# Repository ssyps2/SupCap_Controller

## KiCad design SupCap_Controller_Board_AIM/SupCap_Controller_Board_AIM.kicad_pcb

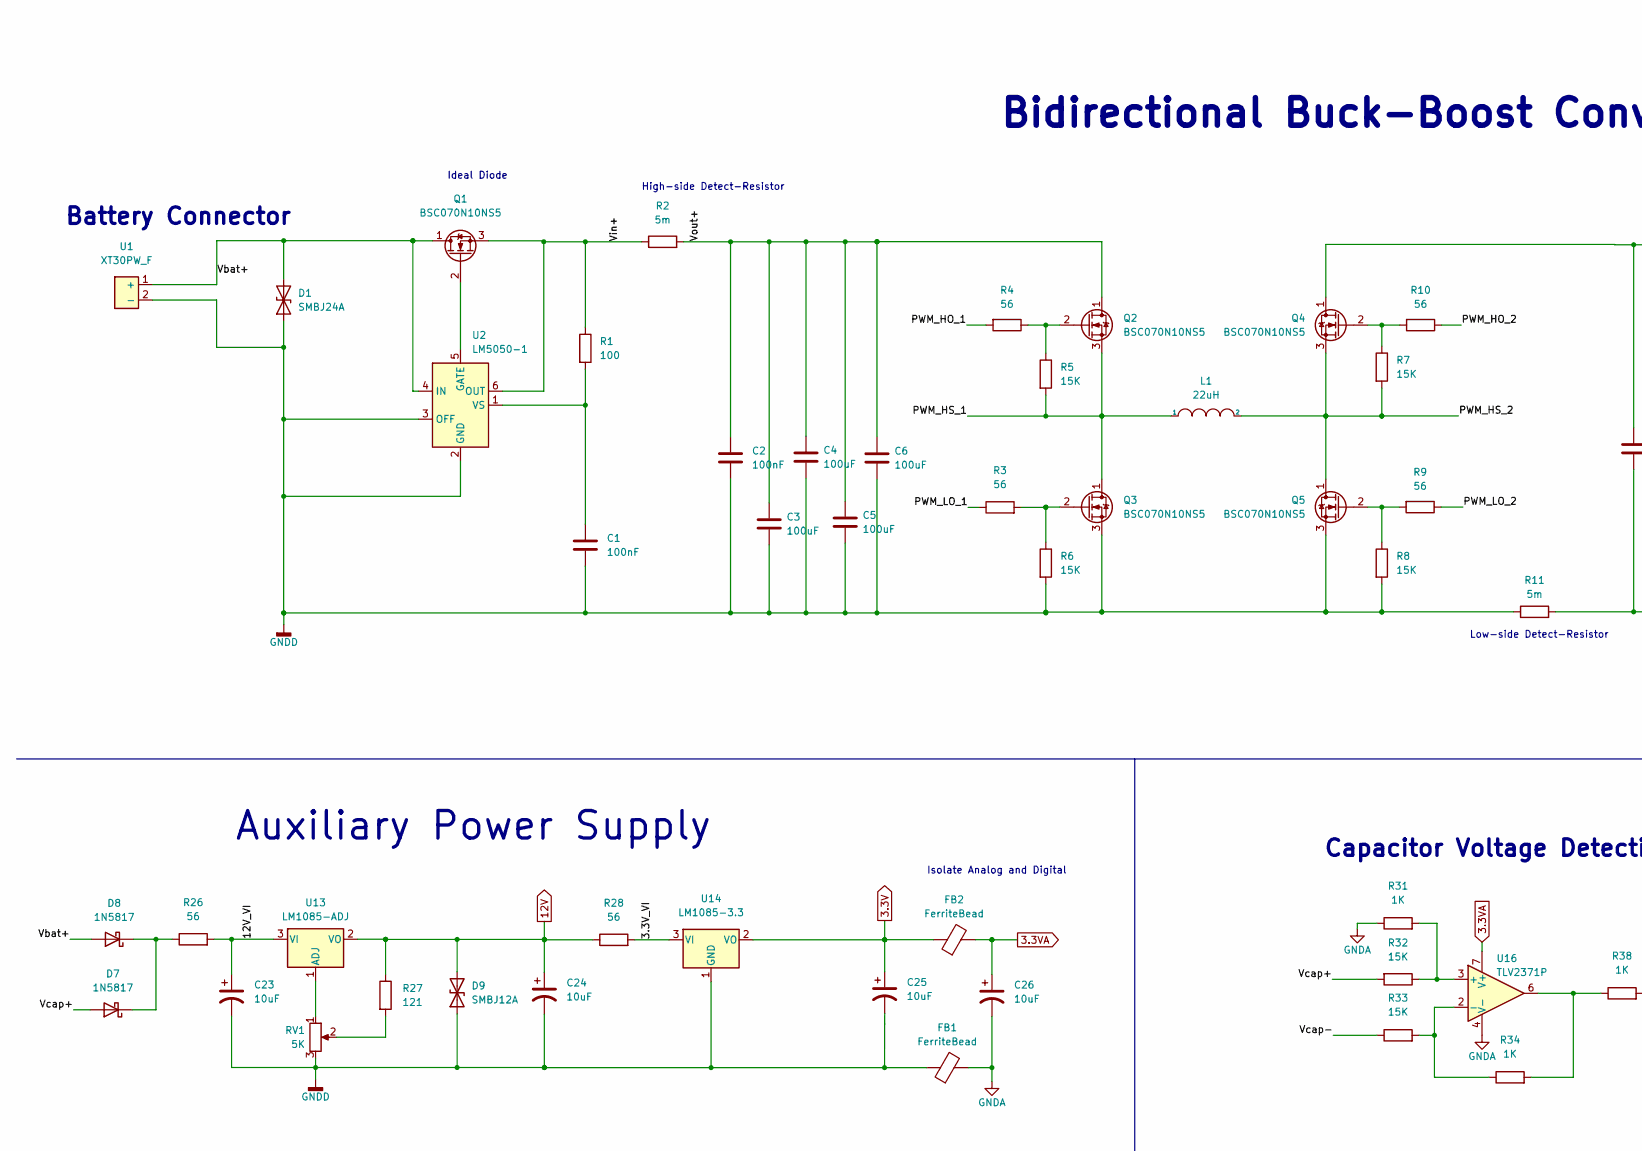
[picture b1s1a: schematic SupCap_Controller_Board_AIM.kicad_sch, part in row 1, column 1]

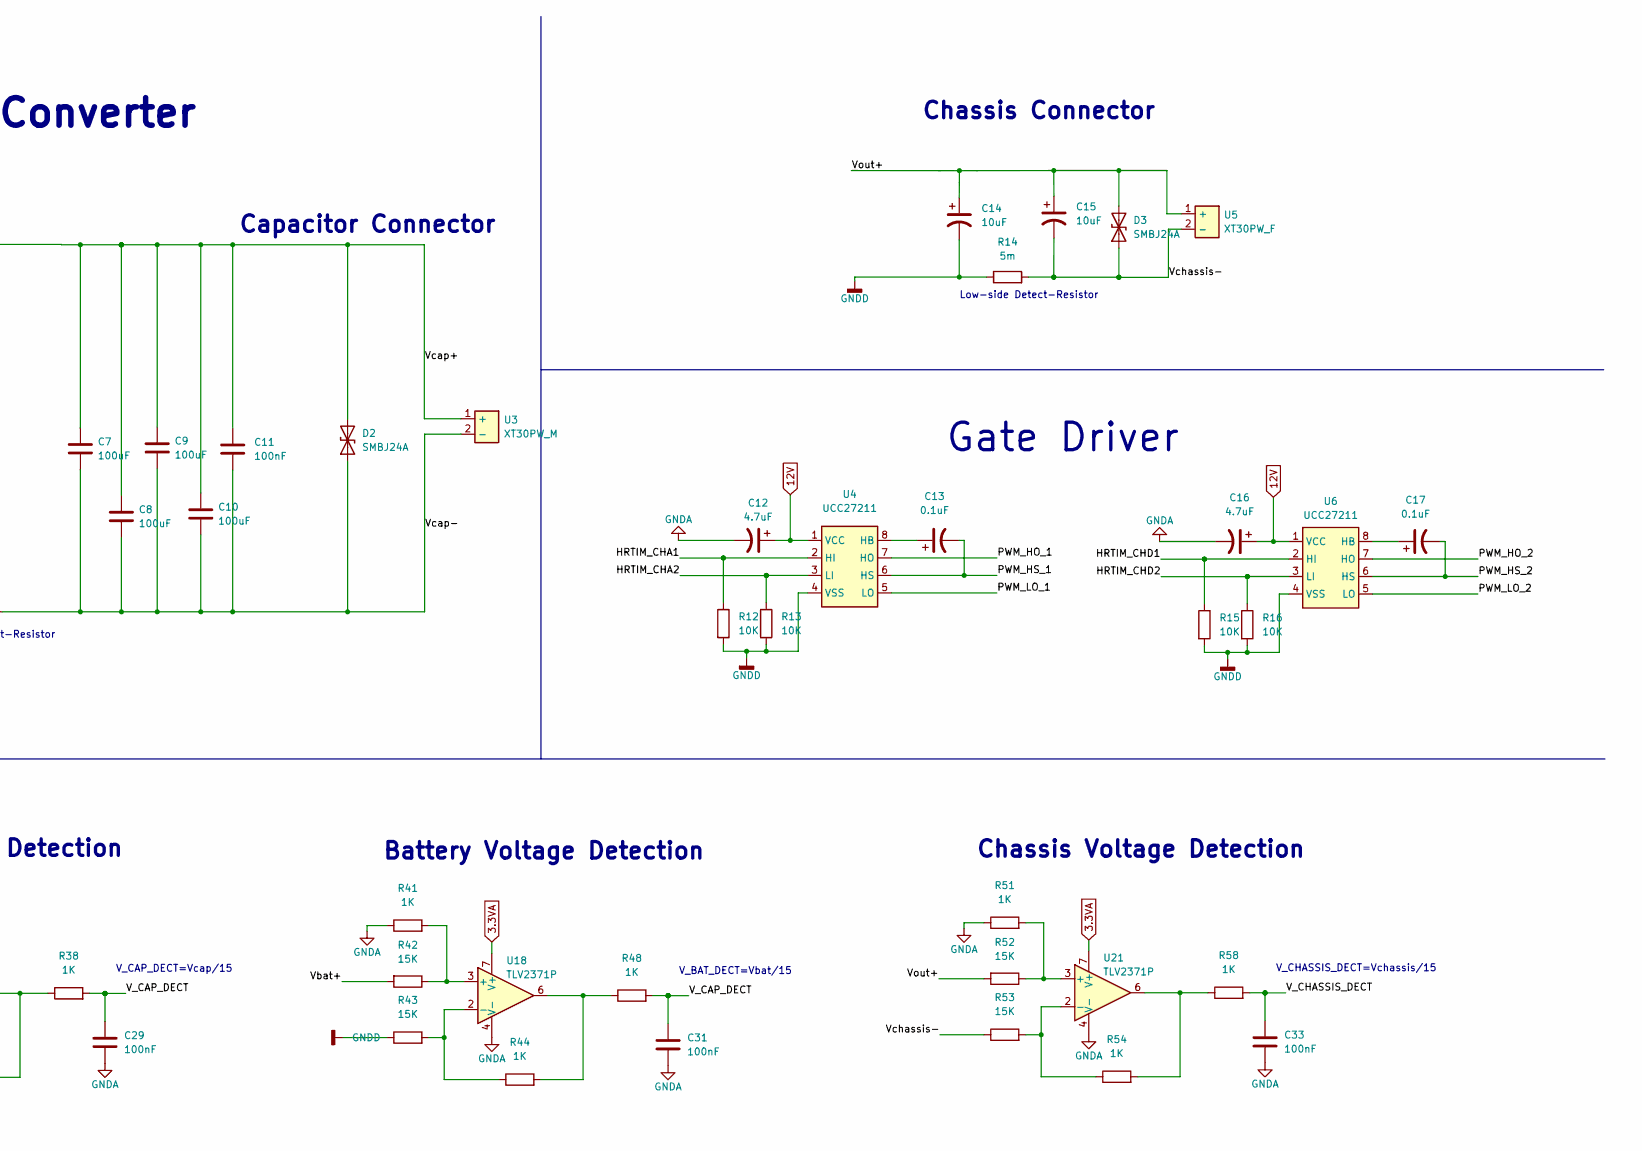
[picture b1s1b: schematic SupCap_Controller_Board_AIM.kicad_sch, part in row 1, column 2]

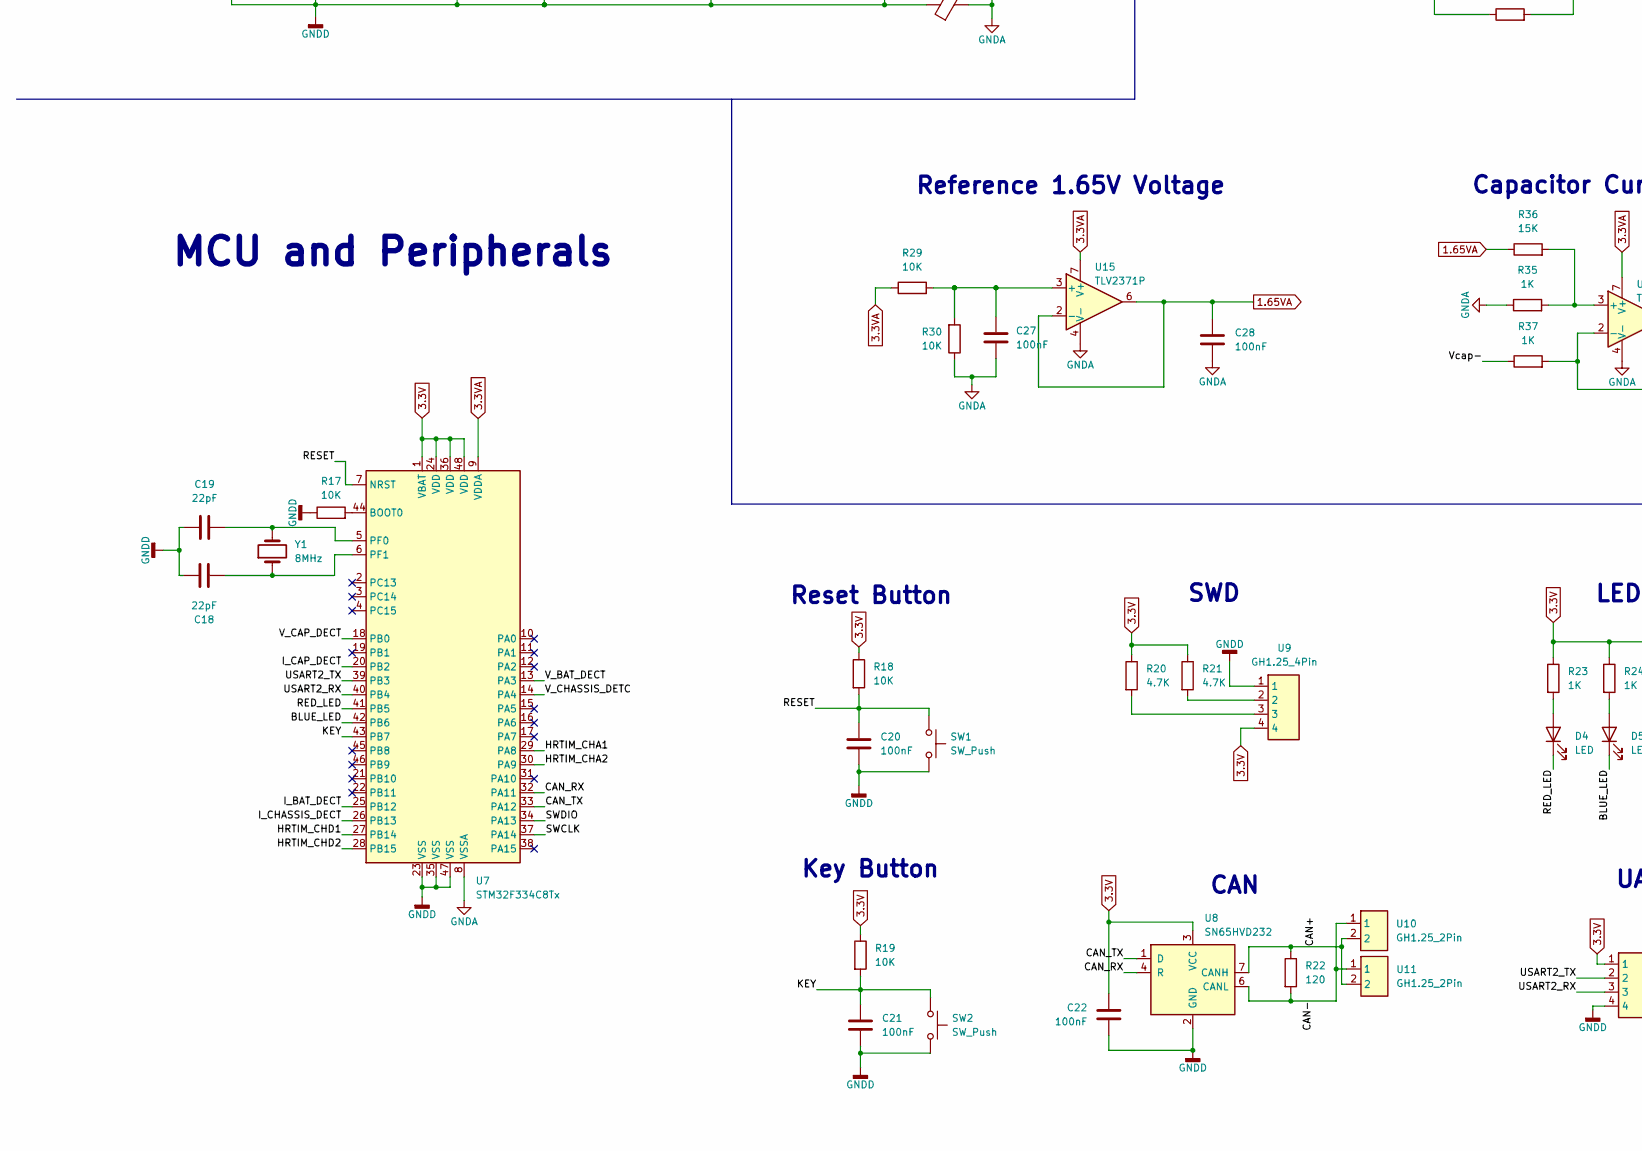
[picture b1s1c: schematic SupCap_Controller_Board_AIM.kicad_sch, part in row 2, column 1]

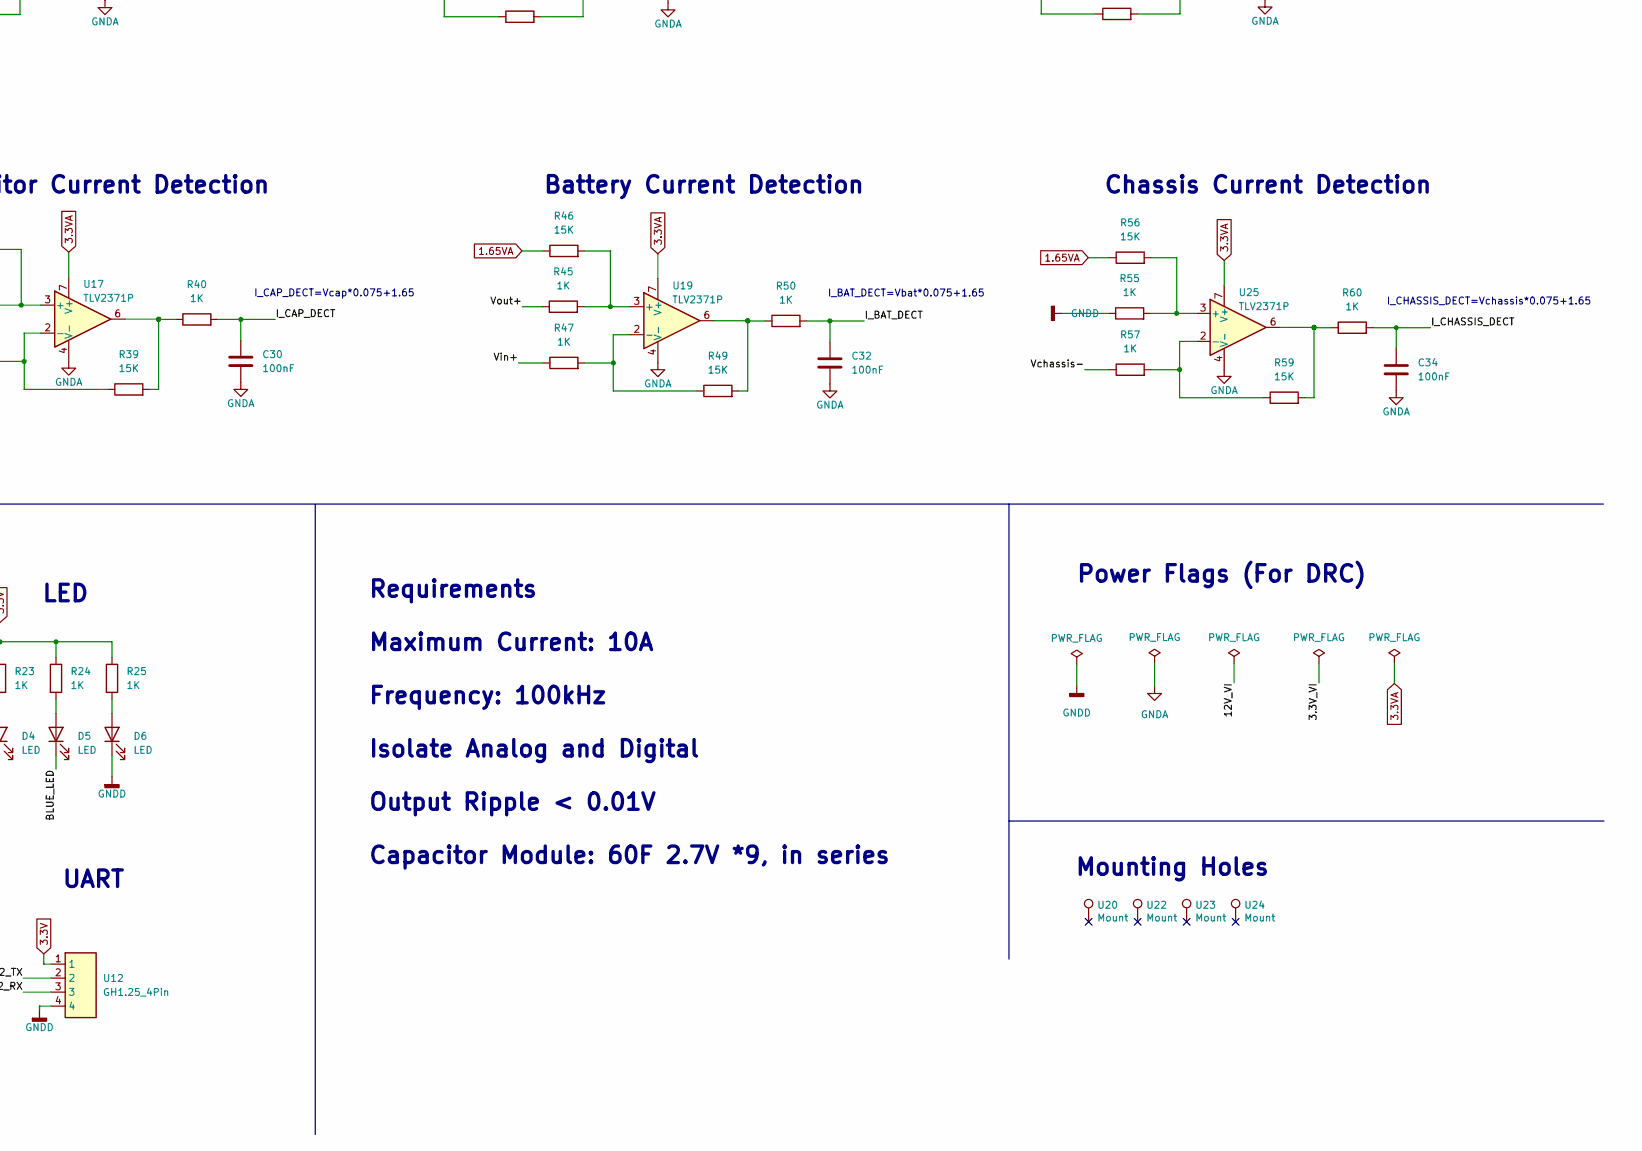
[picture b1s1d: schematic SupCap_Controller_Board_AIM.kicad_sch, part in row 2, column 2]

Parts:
C1, C2, C11, C20, C21, C22, C27, C28, C29, C30, C31, C32, C33, C34: 100nF; C_Disc_D5.0mm_W2.5mm_P5.00mm
C3, C4, C5, C6, C7, C8, C9, C10: 100uF; C_1210_3225Metric
C12, C16: 4.7uF; CP_Radial_D8.0mm_P3.50mm
C13, C17: 0.1uF; CP_Radial_D8.0mm_P3.50mm
C14, C15, C23, C24, C25, C26: 10uF; CP_Radial_D8.0mm_P3.50mm
C18, C19: 22pF; C_Radial_D5.0mm_H5.0mm_P2.00mm
D1, D2, D3: SMBJ24A; D_DO_214AA
D4, D5, D6: LED; LED_0603_1608Metric
D7, D8: 1N5817; D_DO-41_SOD81_P10.16mm_Horizontal
D9: SMBJ12A; D_DO_214AA
FB1, FB2: FerriteBead; R_0603_1608Metric
L1: 22uH; L_Toroid_Vertical_L10.0mm_W20.0mm
Q1, Q2, Q3, Q4, Q5: BSC070N10NS5; Infineon_PG-TDSON-8
R1: 100; R_0603_1608Metric
R2, R11, R14: 5m; R_1206_3216Metric
R3, R4, R9, R10, R26, R28: 56; R_0603_1608Metric
R5, R6, R7, R8, R32, R33, R36, R39, R42, R43, R46, R49, R52, R53, R56, R59: 15K; R_0603_1608Metric
R12, R13, R15, R16, R17, R18, R19, R29, R30: 10K; R_0603_1608Metric
R20, R21: 4.7K; R_0603_1608Metric
R22: 120; R_0603_1608Metric
R23, R24, R25, R31, R34, R35, R37, R38, R40, R41, R44, R45, R47, R48, R50, R51, R54, R55, R57, R58, R60: 1K; R_0603_1608Metric
R27: 121; R_0603_1608Metric
RV1: 5K; Potentiometer_Bourns_3386F_Vertical
SW1, SW2: SW_Push; SW_Push_Button_4Pin_4.5x4.5x3.8mm
U1, U5: XT30PW_F; AMASS_XT30PW-F_1x02_P2.50mm_Horizontal
U2: LM5050-1; TSOT-23-6
U3: XT30PW_M; AMASS_XT30PW-M_1x02_P2.50mm_Horizontal
U4, U6: UCC27211; SOIC-8-1EP_3.9x4.9mm_P1.27mm_EP2.41x3.3mm
U7: STM32F334C8Tx; LQFP-48_7x7mm_P0.5mm
U8: SN65HVD232; SOIC-8_3.9x4.9mm_P1.27mm
U9, U12: GH1.25_4Pin; JST_GH_SM04B-GHS-TB_1x04-1MP_P1.25mm_Horizontal
U10, U11: GH1.25_2Pin; JST_GH_SM02B-GHS-TB_1x02-1MP_P1.25mm_Horizontal
U13: LM1085-ADJ; TO-263-3_TabPin2
U14: LM1085-3.3; TO-263-3_TabPin2
U15, U16, U17, U18, U19, U21, U25: TLV2371P; DIP-8_W7.62mm
U20, U22, U23, U24: Mount; MountingHole_3.2mm_M3_Pad_Via
Y1: 8MHz; Crystal_HC18-U_Vertical

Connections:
1.65VA: C28.1, R36.1, R46.1, R56.1, U15.2 (-), U15.6
3.3V: C22.1, C25.1, FB2.1, R18.1, R19.1, R20.1, R21.1, R23.1, R24.1, R25.1, U7.1 (VBAT), U7.24 (VDD), U7.36 (VDD), U7.48 (VDD), U8.3 (VCC), U9.4, U12.1, U14.2 (VO)
3.3VA: C26.1, FB2.2, R29.1, U7.9 (VDDA), U15.7 (V+), U16.7 (V+), U17.7 (V+), U18.7 (V+), U19.7 (V+), U21.7 (V+), U25.7 (V+)
12V: C12.1, C16.1, C24.1, D9.2 (A2), R27.1, R28.1, U4.1 (VCC), U6.1 (VCC), U13.2 (VO)
/3.3V_VI: R28.2, U14.3 (VI)
/12V_VI: C23.1, R26.2, U13.3 (VI)
/BLUE_LED: D5.1 (K), U7.42 (PB6)
/CAN+: R22.1, U8.7 (CANH), U10.2, U11.2
/CAN-: R22.2, U8.6 (CANL), U10.1, U11.1
/CAN_RX: U7.32 (PA11), U8.4 (R)
/CAN_TX: U7.33 (PA12), U8.1 (D)
/HRTIM_CHA1: R12.1, U4.2 (HI), U7.29 (PA8)
/HRTIM_CHA2: U7.30 (PA9)
/HRTIM_CHD1: R15.1, U6.2 (HI), U7.27 (PB14)
/HRTIM_CHD2: U7.28 (PB15)
/I_BAT_DECT: C32.1, R50.2, U7.25 (PB12)
/I_CAP_DECT: C30.1, R40.2, U7.20 (PB2)
/I_CHASSIS_DECT: C34.1, R60.2, U7.26 (PB13)
/KEY: C21.1, R19.2, SW2.1, U7.43 (PB7)
/PWM_HO_1: R4.2, U4.7 (HO)
/PWM_HO_2: R10.1, U6.7 (HO)
/PWM_HS_1: C13.2, L1.1, Q2.3 (S), Q3.1 (D), R5.2, U4.6 (HS)
/PWM_HS_2: C17.2, L1.2, Q4.3 (S), Q5.1 (D), R7.2, U6.6 (HS)
/PWM_LO_1: R3.1, U4.5 (LO)
/PWM_LO_2: R9.1, U6.5 (LO)
/RED_LED: D4.1 (K), U7.41 (PB5)
/RESET: C20.1, R18.2, SW1.1, U7.7 (NRST)
/SWCLK: U7.37 (PA14)
/SWDIO: U7.34 (PA13)
/USART2_RX: U7.40 (PB4), U12.3
/USART2_TX: U7.39 (PB3), U12.2
/V_BAT_DECT: U7.13 (PA3)
/V_CAP_DECT: C29.1, C31.1, R38.2, R48.2, U7.18 (PB0)
/V_CHASSIS_DECT: C33.1, R58.2
/V_CHASSIS_DETC: U7.14 (PA4)
/Vbat+: D1.2 (A2), D8.2 (A), Q1.1 (D), R42.2, U1.1 (+), U2.4 (IN)
/Vcap+: C7.1, C8.1, C9.1, C10.1, C11.1, D2.2 (A2), D7.2 (A), Q4.1 (D), R32.2, U3.1 (+)
/Vcap-: C7.2, C8.2, C9.2, C10.2, C11.2, D2.1 (A1), R11.2, R33.1, R37.1, U3.2 (-)
/Vchassis-: C15.2, D3.1 (A1), R14.2, R53.1, R57.1, U5.2 (-)
/Vin+: Q1.3 (S), R1.1, R2.1, R47.1, U2.6 (OUT)
/Vout+: C2.1, C3.1, C4.1, C5.1, C6.1, C14.1, C15.1, D3.2 (A2), Q2.1 (D), R2.2, R45.1, R52.2, U5.1 (+)
GNDA: C12.2, C16.2, C26.2, C27.2, C28.2, C29.2, C30.2, C31.2, C32.2, C33.2, C34.2, FB1.2, R30.1, R31.1, R35.1, R41.1, R51.1, U7.8 (VSSA), U15.4 (V-), U16.4 (V-), U17.4 (V-), U18.4 (V-), U19.4 (V-), U21.4 (V-), U25.4 (V-)
GNDD: C1.2, C2.2, C3.2, C4.2, C5.2, C6.2, C14.2, C18.2, C19.2, C20.2, C21.2, C22.2, C23.2, C24.2, C25.2, D1.1 (A1), D6.1 (K), D9.1 (A1), FB1.1, Q3.3 (S), Q5.3 (S), R6.2, R8.2, R11.1, R12.2, R13.2, R14.1, R15.2, R16.2, R17.1, R43.1, R55.1, RV1.3, SW1.2, SW2.2, U1.2 (-), U2.2 (GND), U2.3 (OFF), U4.4 (VSS), U6.4 (VSS), U7.23 (VSS), U7.35 (VSS), U7.47 (VSS), U8.2 (GND), U9.1, U12.4, U14.1 (GND)
unnamed: C1.1, R1.2, U2.1 (VS)
unnamed: C13.1, U4.8 (HB)
unnamed: C17.1, U6.8 (HB)
unnamed: C18.1, U7.6 (PF1), Y1.1
unnamed: C19.1, U7.5 (PF0), Y1.2
unnamed: C27.1, U15.3 (+)
unnamed: D4.2 (A), R23.2
unnamed: D5.2 (A), R24.2
unnamed: D6.2 (A), R25.2
unnamed: D7.1 (K), D8.1 (K), R26.1
unnamed: Q1.2 (G), U2.5 (GATE)
unnamed: Q2.2 (G), R4.1, R5.1
unnamed: Q3.2 (G), R3.2, R6.1
unnamed: Q4.2 (G), R7.1, R10.2
unnamed: Q5.2 (G), R8.1, R9.2
unnamed: R13.1, U4.3 (LI)
unnamed: R16.1, U6.3 (LI)
unnamed: R17.2, U7.44 (BOOT0)
unnamed: R20.2, U9.3
unnamed: R21.2, U9.2
unnamed: R27.2, RV1.2
unnamed: R29.2, R30.2
unnamed: R31.2, R32.1, U16.3 (+)
unnamed: R33.2, R34.1, U16.2 (-)
unnamed: R34.2, R38.1, U16.6
unnamed: R35.2, R36.2, U17.3 (+)
unnamed: R37.2, R39.1, U17.2 (-)
unnamed: R39.2, R40.1, U17.6
unnamed: R41.2, R42.1, U18.3 (+)
unnamed: R43.2, R44.1, U18.2 (-)
unnamed: R44.2, R48.1, U18.6
unnamed: R45.2, R46.2, U19.3 (+)
unnamed: R47.2, R49.1, U19.2 (-)
unnamed: R49.2, R50.1, U19.6
unnamed: R51.2, R52.1, U21.3 (+)
unnamed: R53.2, R54.1, U21.2 (-)
unnamed: R54.2, R58.1, U21.6
unnamed: R55.2, R56.2, U25.3 (+)
unnamed: R57.2, R59.1, U25.2 (-)
unnamed: R59.2, R60.1, U25.6
unnamed: RV1.1, U13.1 (ADJ)

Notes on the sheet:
Gate Driver
I_BAT_DECT=Vbat*0.075+1.65
LED
Low-side Detect-Resistor
Capacitor Current Detection
Capacitor Connector
Chassis Connector
Battery Connector
Auxiliary Power Supply
Capacitor Voltage Detection
Reference 1.65V Voltage
High-side Detect-Resistor
Ideal Diode
V_CHASSIS_DECT=Vchassis/15
CAN
SWD
I_CHASSIS_DECT=Vchassis*0.075+1.65
Mounting Holes
V_BAT_DECT=Vbat/15
Key Button
V_CAP_DECT=Vcap/15
I_CAP_DECT=Vcap*0.075+1.65
Battery Current Detection
Bidirectional Buck-Boost Converter
Requirements Maximum Current: 10A Frequency: 100kHz Isolate Analog and Digital Output Ripple < 0.01V Capacitor Module: 60F 2.7V *9, in series
Power Flags (For DRC)
Chassis Voltage Detection
Isolate Analog and Digital
Reset Button
MCU and Peripherals
Chassis Current Detection
UART
Battery Voltage Detection

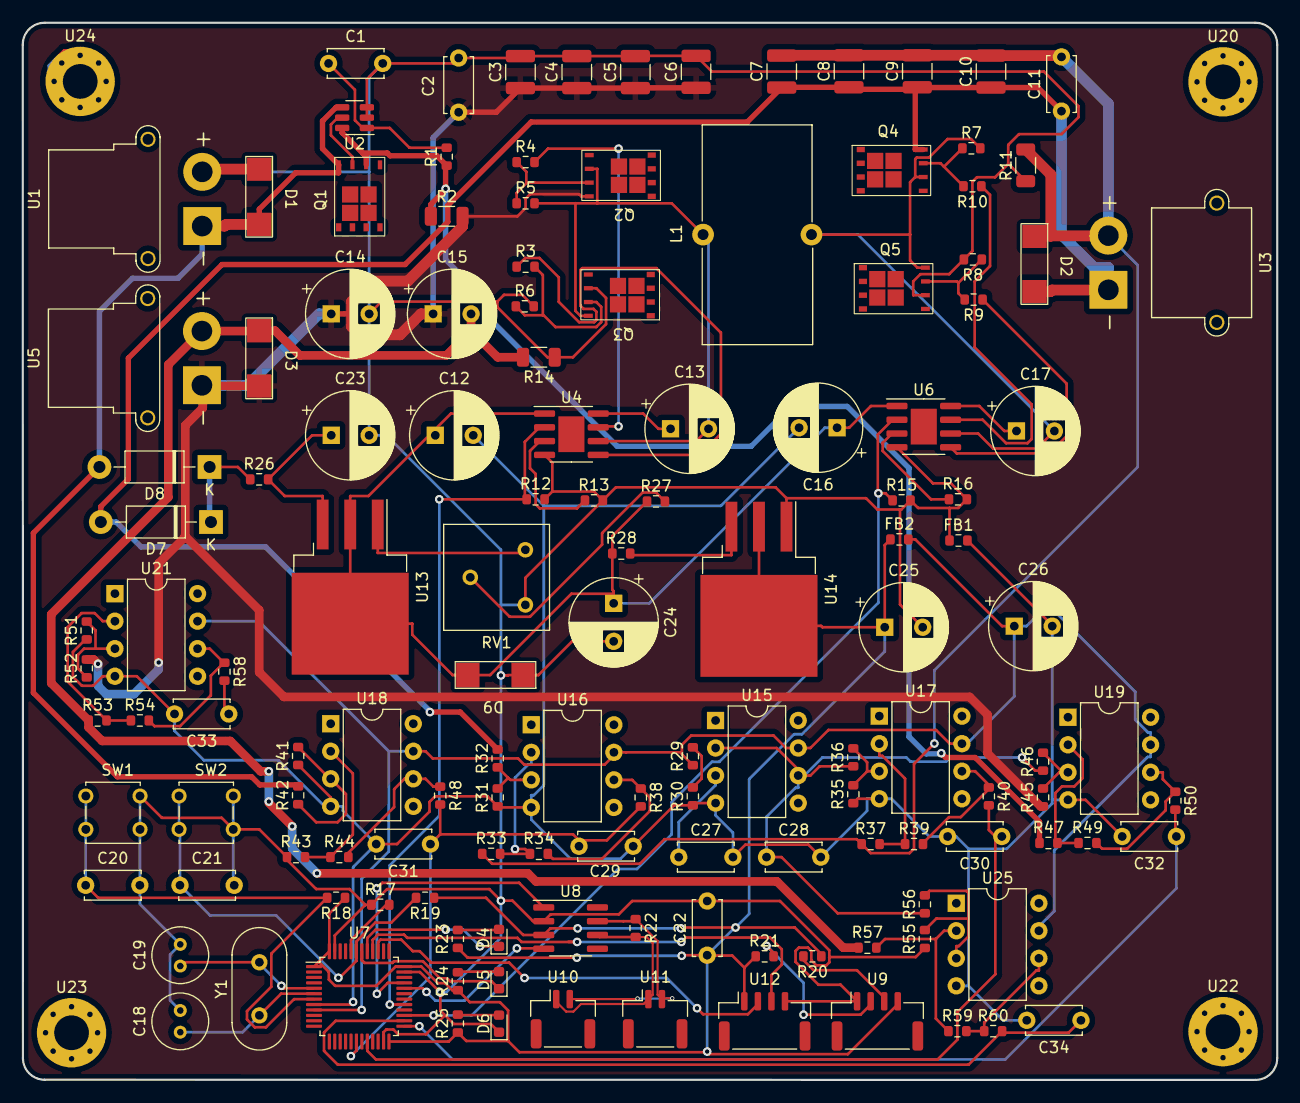
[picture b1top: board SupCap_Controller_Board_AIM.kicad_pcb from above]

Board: 2 copper layers, 115.7 x 97.5 mm, 140 parts (0 on the bottom side), 78 nets.

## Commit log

2023-11-18 upload the SupCap control board project and PLECS simulation files
